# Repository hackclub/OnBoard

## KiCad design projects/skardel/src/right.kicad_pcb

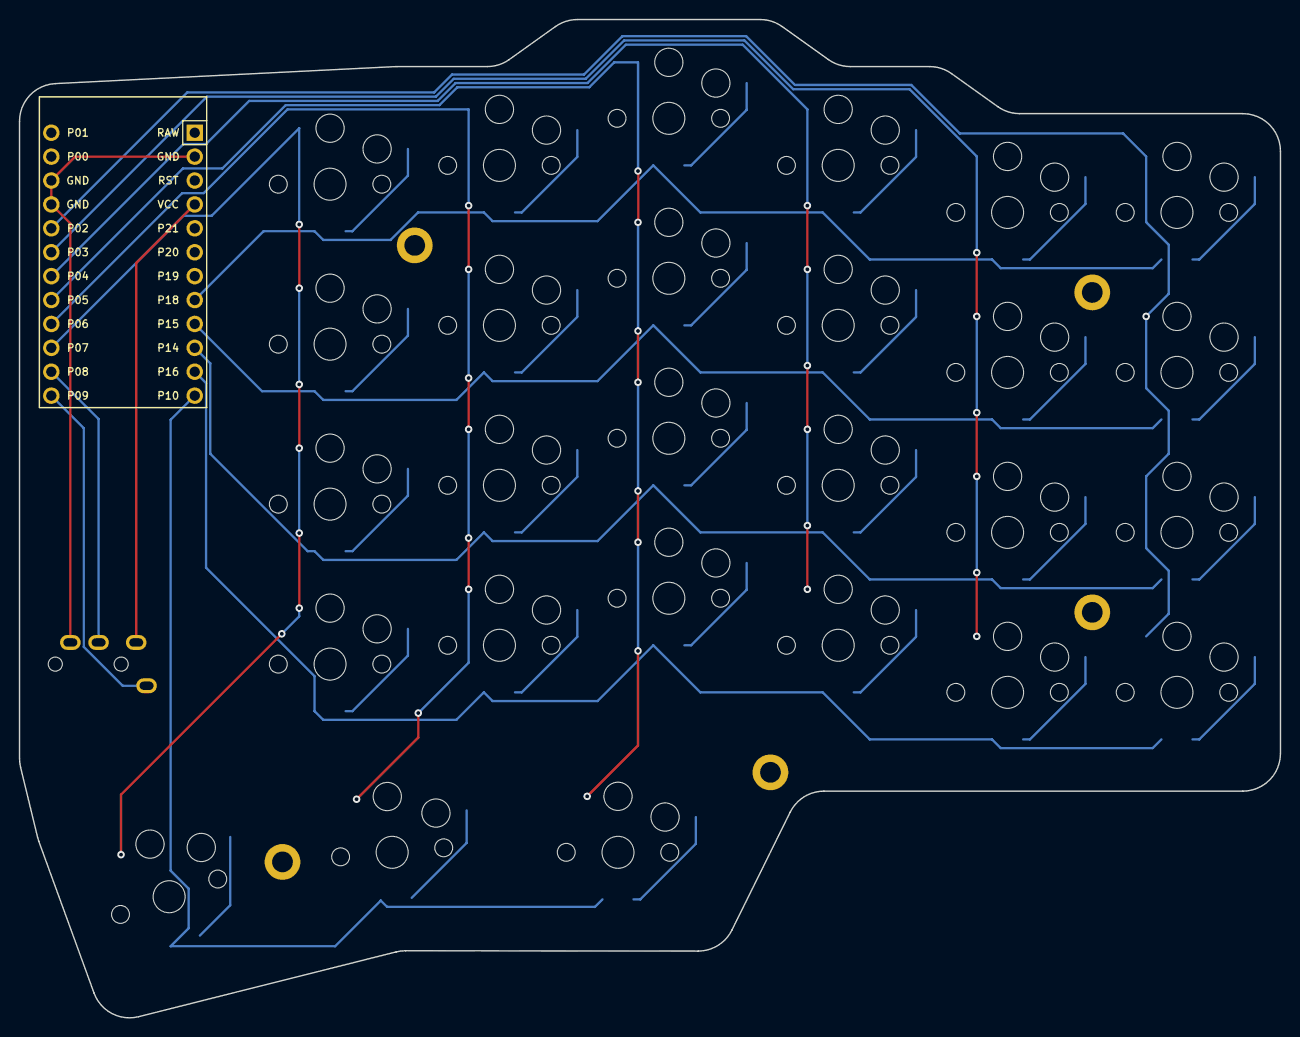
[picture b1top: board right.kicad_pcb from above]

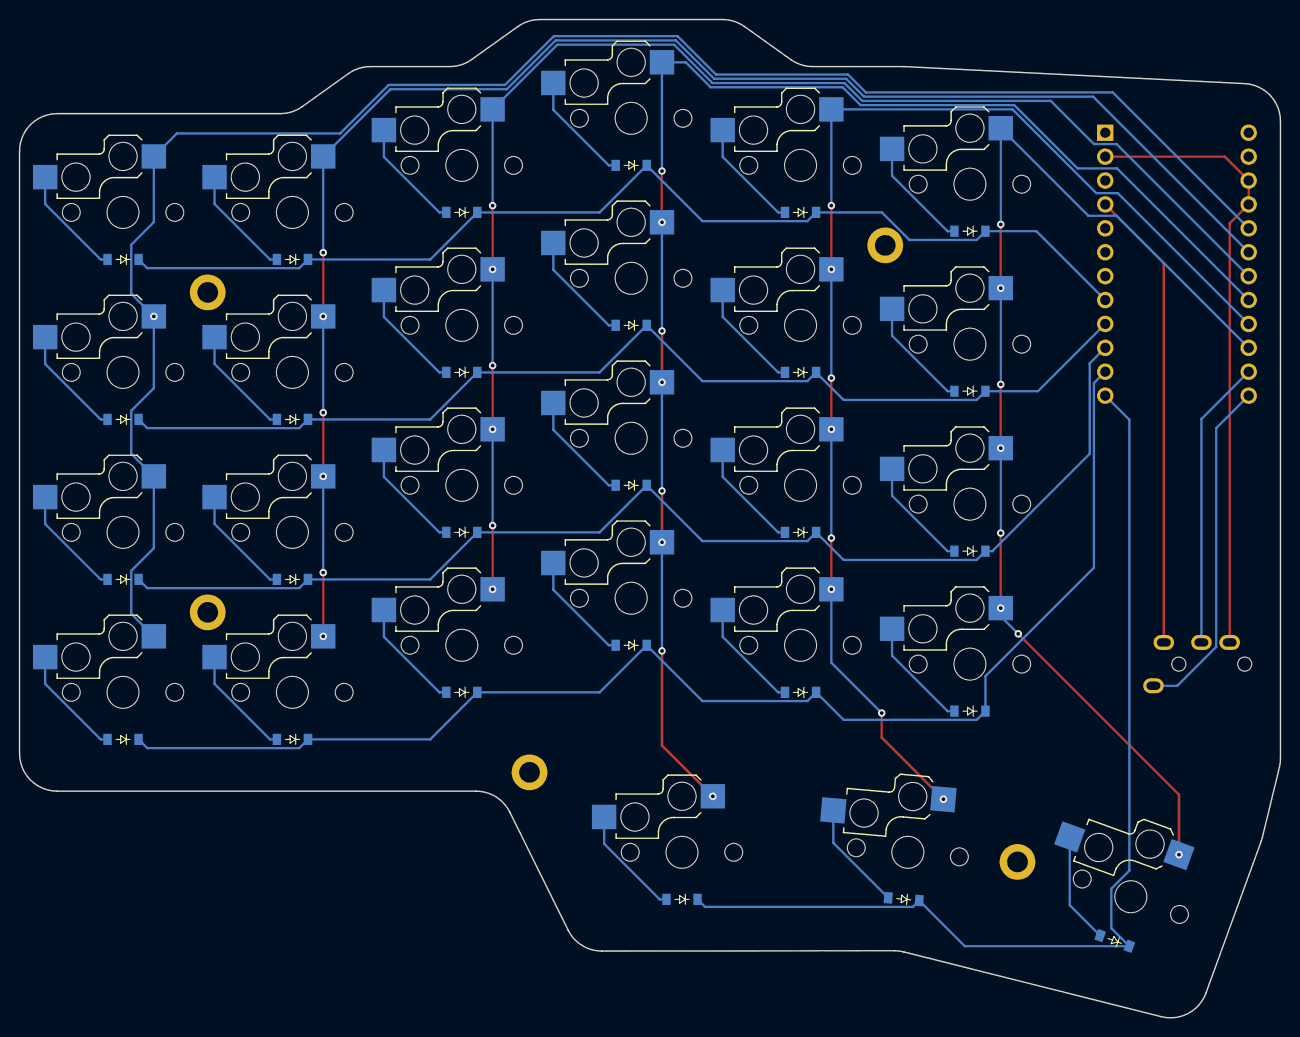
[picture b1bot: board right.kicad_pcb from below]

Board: 2 copper layers, 134.0 x 106.1 mm, 61 parts (54 on the bottom side), 42 nets.

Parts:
D1, D2, D3, D4, D5, D6, D7, D8, D9, D10, D11, D12, D13, D14, D15, D16, D17, D18, D19, D20, D21, D22, D23, D24, D25, D26, D27: diode_tht_sod123
H1, H2, H3, H4, H5: mounting_hole_plated
MCU1: ProMicro
S1, S2, S3, S4, S5, S6, S7, S8, S9, S10, S11, S12, S13, S14, S15, S16, S17, S18, S19, S20, S21, S22, S23, S24, S25, S26, S27: switch_choc_v1_v2
TRRS1: trrs_pj320a

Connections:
GND: MCU1.2, MCU1.15, MCU1.16, TRRS1.2
P2: MCU1.17, S1.1, S2.1, S3.1, S4.1
P3: MCU1.18, S5.1, S6.1, S7.1, S8.1
P4: MCU1.19, S9.1, S10.1, S11.1, S12.1
P5: MCU1.20, S13.1, S14.1, S15.1, S16.1, S25.1
P6: MCU1.21, S17.1, S18.1, S19.1, S20.1, S26.1
P7: MCU1.22, S21.1, S22.1, S23.1, S24.1, S27.1
P8: MCU1.23, TRRS1.3
P9: MCU1.24, TRRS1.5
P10: D25.1, D26.1, D27.1, MCU1.12
P14: D2.1, D6.1, D10.1, D14.1, D18.1, D22.1, MCU1.10
P15: D3.1, D7.1, D11.1, D15.1, D19.1, D23.1, MCU1.9
P16: D1.1, D5.1, D9.1, D13.1, D17.1, D21.1, MCU1.11
P18: D4.1, D8.1, D12.1, D16.1, D20.1, D24.1, MCU1.8
VCC: MCU1.4, TRRS1.4
mirror_home_home: D26.2, S26.2
mirror_in_home: D27.2, S27.2
mirror_index_bottom: D17.2, S17.2
mirror_index_home: D18.2, S18.2
mirror_index_num: D20.2, S20.2
mirror_index_top: D19.2, S19.2
mirror_inner_bottom: D21.2, S21.2
mirror_inner_home: D22.2, S22.2
mirror_inner_num: D24.2, S24.2
mirror_inner_top: D23.2, S23.2
mirror_middle_bottom: D13.2, S13.2
mirror_middle_home: D14.2, S14.2
mirror_middle_num: D16.2, S16.2
mirror_middle_top: D15.2, S15.2
mirror_out_home: D25.2, S25.2
mirror_outer_bottom: D1.2, S1.2
mirror_outer_home: D2.2, S2.2
mirror_outer_num: D4.2, S4.2
mirror_outer_top: D3.2, S3.2
mirror_pinky_bottom: D5.2, S5.2
mirror_pinky_home: D6.2, S6.2
mirror_pinky_num: D8.2, S8.2
mirror_pinky_top: D7.2, S7.2
mirror_ring_bottom: D9.2, S9.2
mirror_ring_home: D10.2, S10.2
mirror_ring_num: D12.2, S12.2
mirror_ring_top: D11.2, S11.2

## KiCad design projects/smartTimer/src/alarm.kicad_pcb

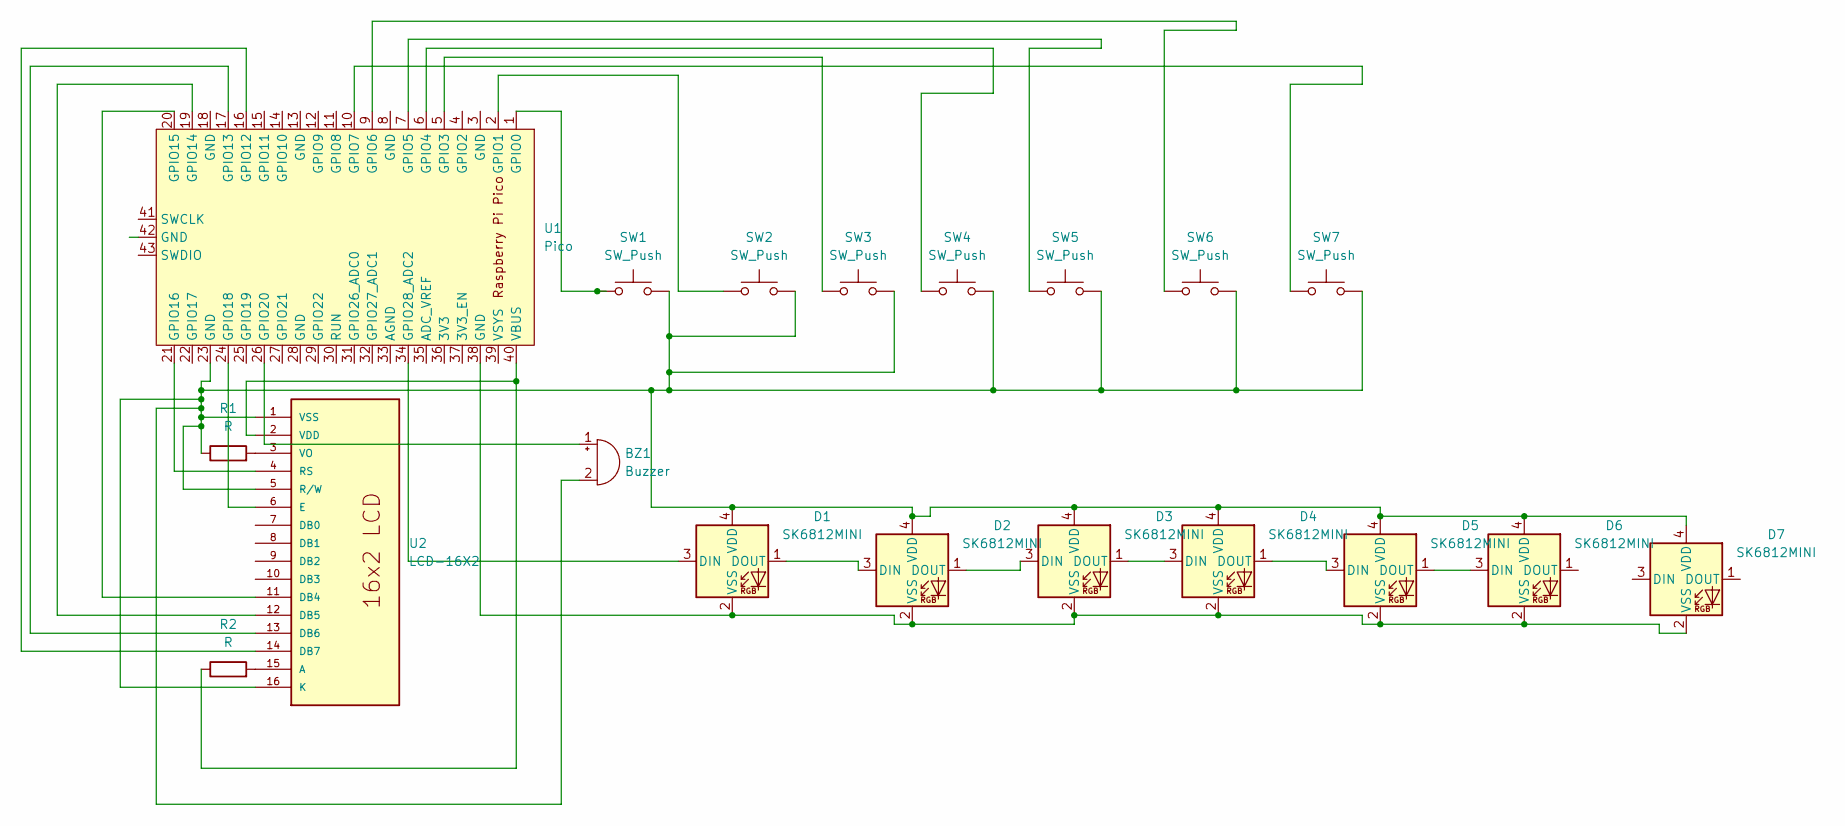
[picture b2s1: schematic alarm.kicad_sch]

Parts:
BZ1: Buzzer; Buzzer_12x9.5RM7.6
D1, D2, D3, D4, D5, D6, D7: SK6812MINI; LED_SK6812MINI_PLCC4_3.5x3.5mm_P1.75mm
R1, R2: R; R_Axial_DIN0204_L3.6mm_D1.6mm_P5.08mm_Horizontal
SW1, SW2, SW3, SW4, SW5, SW6, SW7: SW_Push; SW_PUSH_6mm
U1: Pico; RaspberryPi_Pico_W_SMD
U2: LCD-16X2; MODULE_LCD-16X2; PARTREV N/A

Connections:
unnamed: BZ1.1 (+), U1.26 (GPIO20)
unnamed: BZ1.2 (-), D1.4 (VDD), D2.4 (VDD), D3.4 (VDD), D4.4 (VDD), D5.4 (VDD), D6.4 (VDD), D7.4 (VDD), R1.1, SW1.2, SW2.2, SW3.2, SW4.2, SW5.2, SW6.2, SW7.2, U1.23 (GND), U2.1 (VSS), U2.5 (R/W), U2.16 (K)
unnamed: D1.3 (DIN), U1.34 (GPIO28_ADC2)
unnamed: D1.1 (DOUT), D2.3 (DIN)
unnamed: D1.2 (VSS), D2.2 (VSS), D3.2 (VSS), D4.2 (VSS), D5.2 (VSS), D6.2 (VSS), D7.2 (VSS), U1.38 (GND)
unnamed: D2.1 (DOUT), D3.3 (DIN)
unnamed: D3.1 (DOUT), D4.3 (DIN)
unnamed: D4.1 (DOUT), D5.3 (DIN)
unnamed: D5.1 (DOUT), D6.3 (DIN)
unnamed: SW1.1, U1.1 (GPIO0)
unnamed: SW2.1, U1.2 (GPIO1)
unnamed: SW3.1, U1.5 (GPIO3)
unnamed: SW4.1, U1.6 (GPIO4)
unnamed: SW5.1, U1.7 (GPIO5)
unnamed: SW6.1, U1.9 (GPIO6)
unnamed: SW7.1, U1.10 (GPIO7)
unnamed: U1.16 (GPIO12), U2.14 (DB7)
unnamed: U1.17 (GPIO13), U2.13 (DB6)
unnamed: U1.19 (GPIO14), U2.12 (DB5)
unnamed: U1.20 (GPIO15), U2.11 (DB4)
unnamed: U1.21 (GPIO16), U2.4 (RS)
unnamed: U1.24 (GPIO18), U2.6 (E)
unnamed: R2.1, U1.40 (VBUS), U2.2 (VDD)
unnamed: R2.2, U2.15 (A)
unnamed: R1.2, U2.3 (VO)

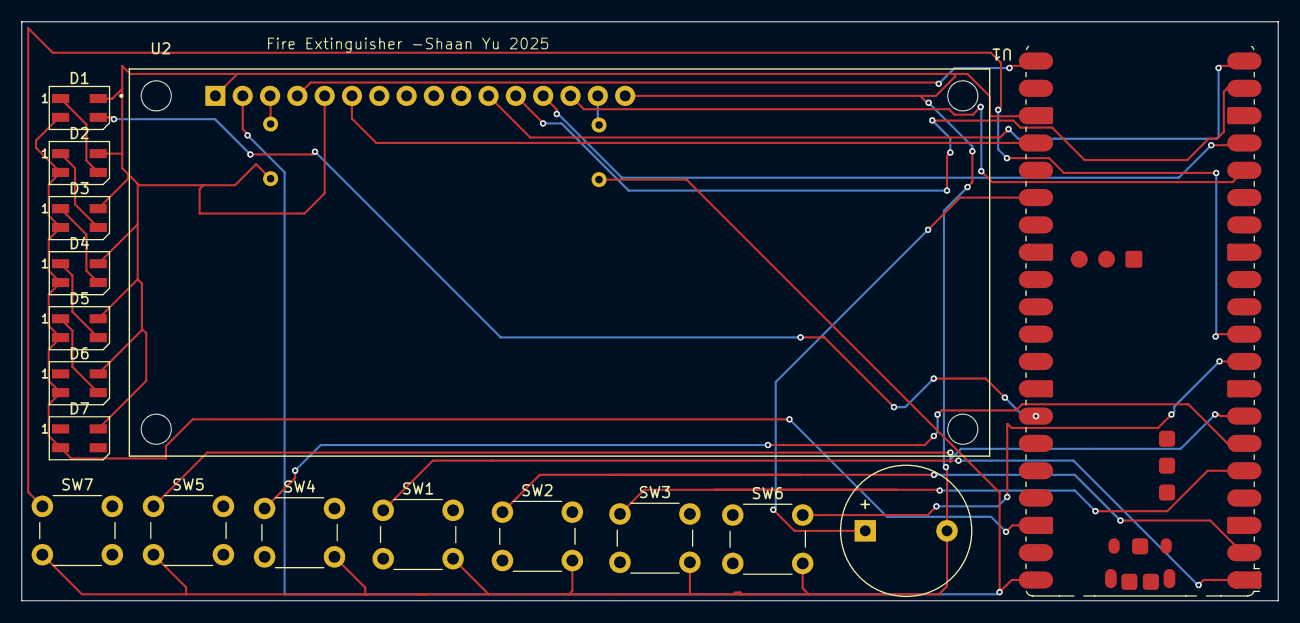
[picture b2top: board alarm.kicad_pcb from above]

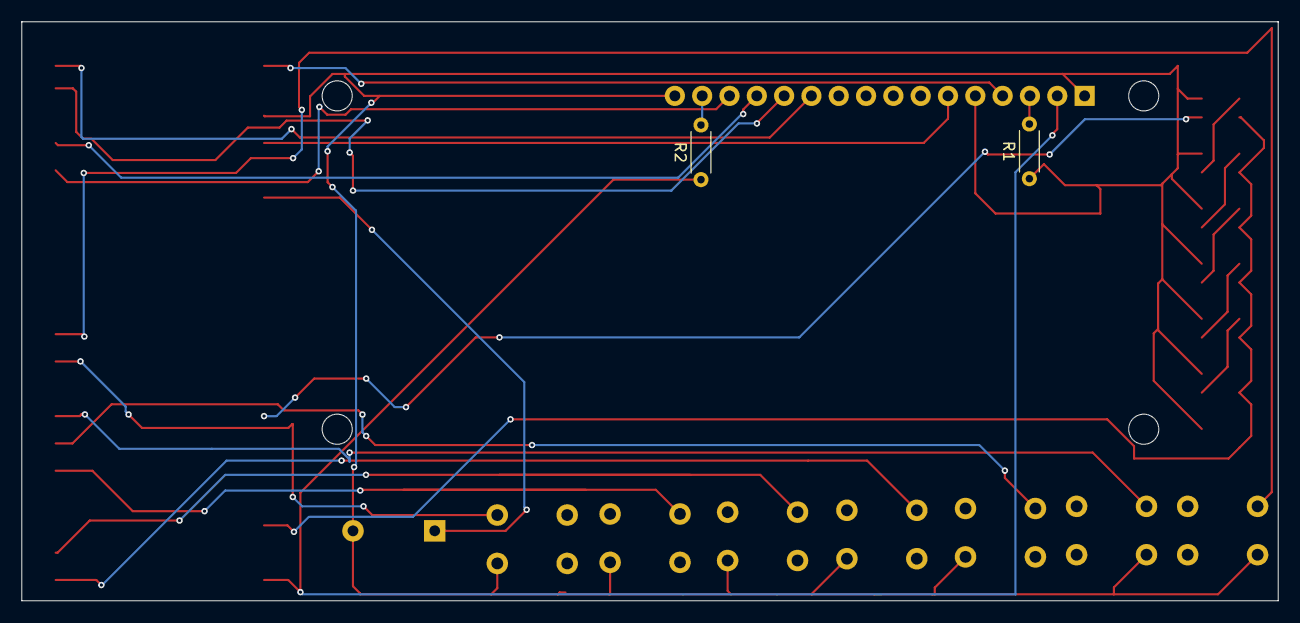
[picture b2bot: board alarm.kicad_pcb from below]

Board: 2 copper layers, 116.8 x 53.8 mm, 19 parts (2 on the bottom side), 25 nets.

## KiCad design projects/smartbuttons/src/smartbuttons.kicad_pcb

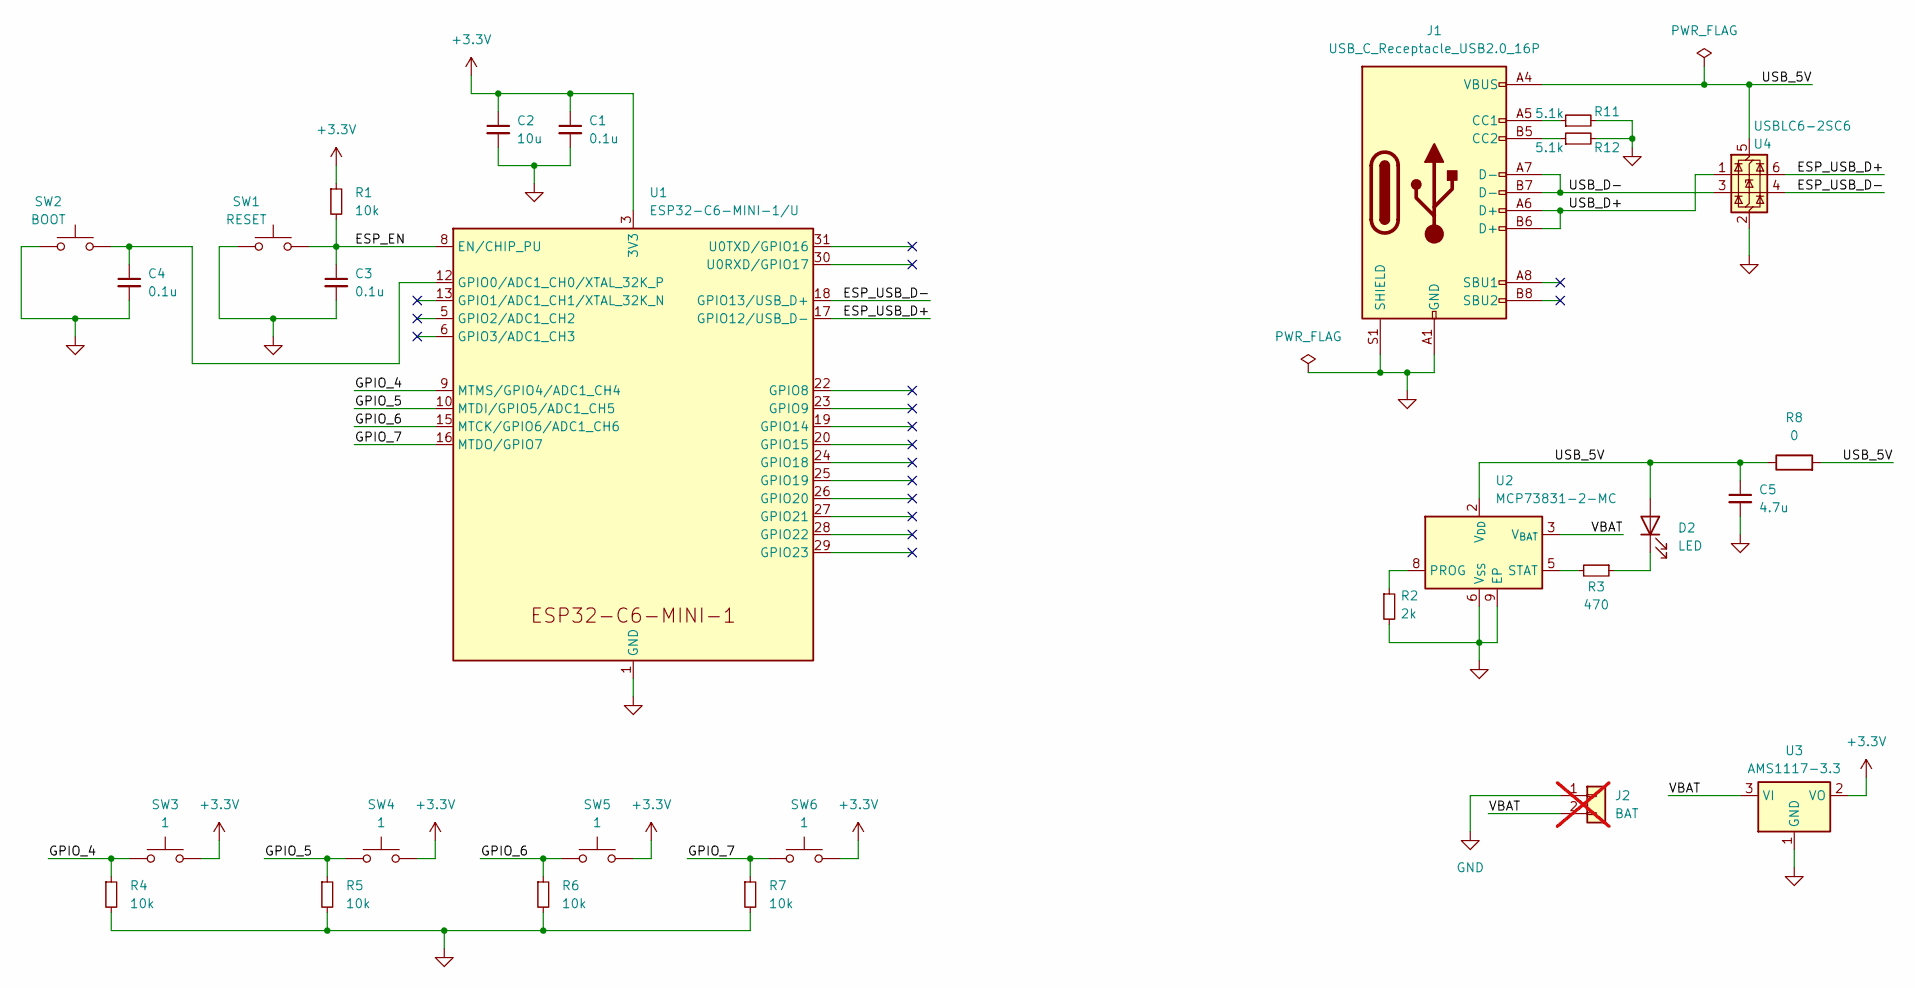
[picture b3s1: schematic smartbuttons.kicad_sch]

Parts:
C1, C3, C4: 0.1u; C_0402_1005Metric; LCSC C1525
C2: 10u; C_0805_2012Metric; LCSC C440198
C5: 4.7u; C_0805_2012Metric; LCSC C1779
D2: LED; LED_0805_2012Metric; LCSC C2296
J1: USB_C_Receptacle_USB2.0_16P; USB_C_Receptacle_HCTL_HC-TYPE-C-16P-01A; LCSC C2894897
J2: BAT; SolderWirePad_3; not fitted
R1, R4, R5, R6, R7: 10k; R_0402_1005Metric; LCSC C25744
R2: 2k; R_0402_1005Metric; LCSC C4109
R3: 470; R_0402_1005Metric; LCSC C25117
R8: 0; R_0805_2012Metric; LCSC C431818
R11, R12: 5.1k; R_0402_1005Metric; LCSC C25905
SW1: RESET; SW-SMD_L3.9-W3.0-P4.45; LCSC C115357
SW2: BOOT; SW-SMD_L3.9-W3.0-P4.45; LCSC C115357
SW3, SW4, SW5, SW6: 1; SW_Kailh_Choc_V1_THT; LCSC C400229
U1: ESP32-C6-MINI-1/U; ESP32-C6-MINI-1; LCSC C5736265
U2: MCP73831-2-MC; DFN-8-1EP_3x2mm_P0.5mm_EP1.7x1.4mm; LCSC C635037
U3: AMS1117-3.3; SOT-223-3_TabPin2; LCSC C6186
U4: USBLC6-2SC6; SOT-23-6; LCSC C7519

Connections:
+3.3V: C1.1, C2.1, R1.1, SW3.2, SW4.2, SW5.2, SW6.2, U1.3 (3V3), U3.2 (VO)
/ESP_EN: C3.1, R1.2, SW1.2, U1.8 (EN/CHIP_PU)
/ESP_USB_D+: U1.17 (GPIO12/USB_D-), U4.6 (I/O1)
/ESP_USB_D-: U1.18 (GPIO13/USB_D+), U4.4 (I/O2)
/GPIO_4: R4.1, SW3.1, U1.9 (MTMS/GPIO4/ADC1_CH4)
/GPIO_5: R5.1, SW4.1, U1.10 (MTDI/GPIO5/ADC1_CH5)
/GPIO_6: R6.1, SW5.1, U1.15 (MTCK/GPIO6/ADC1_CH6)
/GPIO_7: R7.1, SW6.1, U1.16 (MTDO/GPIO7)
/USB_5V: C5.1, D2.2 (A), J1.A4 (VBUS), J1.A9 (VBUS), J1.B4 (VBUS), J1.B9 (VBUS), R8.1, R8.2, U2.1 (V_{DD}), U2.2 (V_{DD}), U4.5 (VBUS)
/USB_D+: J1.A6 (D+), J1.B6 (D+), U4.1 (I/O1)
/USB_D-: J1.A7 (D-), J1.B7 (D-), U4.3 (I/O2)
/VBAT: J2.2, U2.3 (V_{BAT}), U2.4 (V_{BAT}), U3.3 (VI)
GND: C1.2, C2.2, C3.2, C4.2, C5.2, J1.A1 (GND), J1.A12 (GND), J1.B1 (GND), J1.B12 (GND), J1.S1 (SHIELD), J2.1, R2.2, R4.2, R5.2, R6.2, R7.2, R11.2, R12.2, SW1.1, SW2.1, U1.1 (GND), U1.2 (GND), U1.11 (GND), U1.14 (GND), U1.36 (GND), U1.37 (GND), U1.38 (GND), U1.39 (GND), U1.40 (GND), U1.41 (GND), U1.42 (GND), U1.43 (GND), U1.44 (GND), U1.45 (GND), U1.46 (GND), U1.47 (GND), U1.48 (GND), U1.49 (GND), U1.50 (GND), U1.51 (GND), U1.52 (GND), U1.53 (GND), U2.6 (V_{SS}), U2.9 (EP), U3.1 (GND), U4.2 (GND)
unnamed: D2.1 (K), R3.1
unnamed: J1.A5 (CC1), R11.1
unnamed: J1.B5 (CC2), R12.1
unnamed: C4.1, SW2.2, U1.12 (GPIO0/ADC1_CH0/XTAL_32K_P)
unnamed: R2.1, U2.8 (PROG)
unnamed: R3.2, U2.5 (STAT)

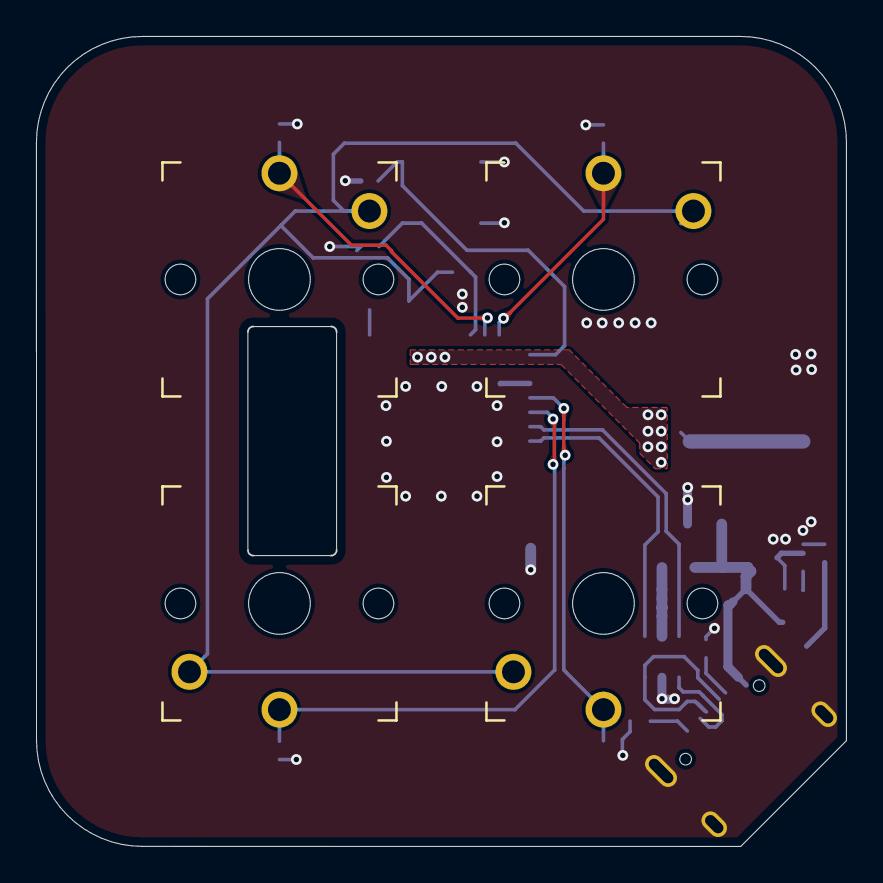
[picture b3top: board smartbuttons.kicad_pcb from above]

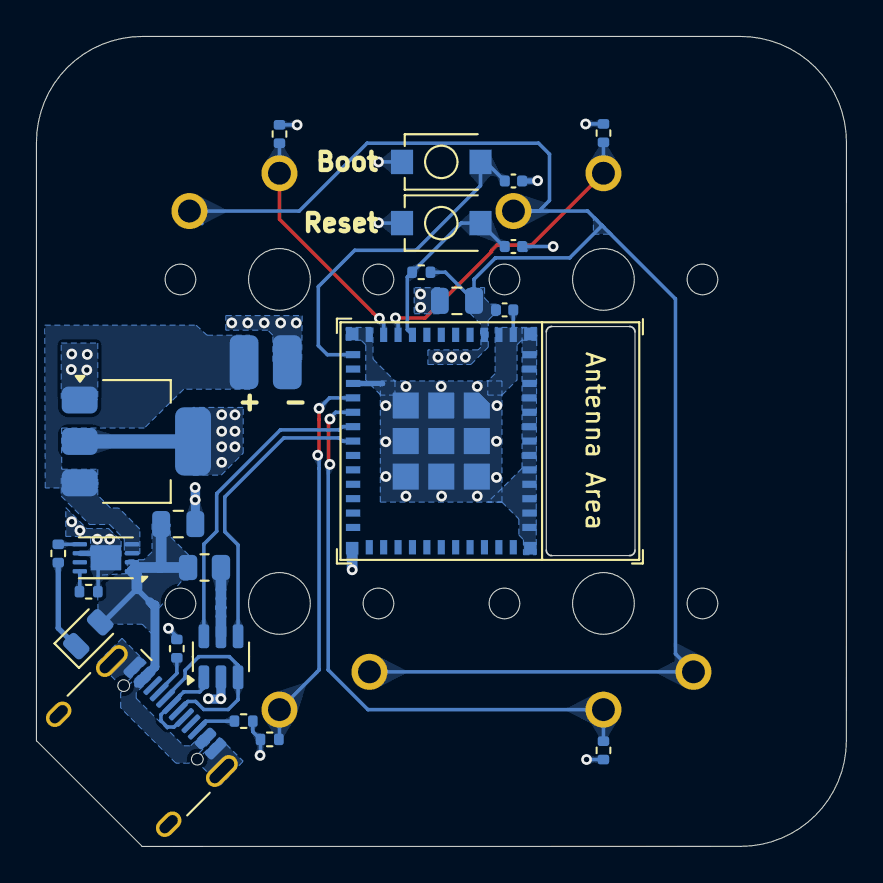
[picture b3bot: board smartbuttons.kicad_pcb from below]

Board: 2 copper layers, 45.0 x 45.0 mm, 28 parts (24 on the bottom side), 19 nets.

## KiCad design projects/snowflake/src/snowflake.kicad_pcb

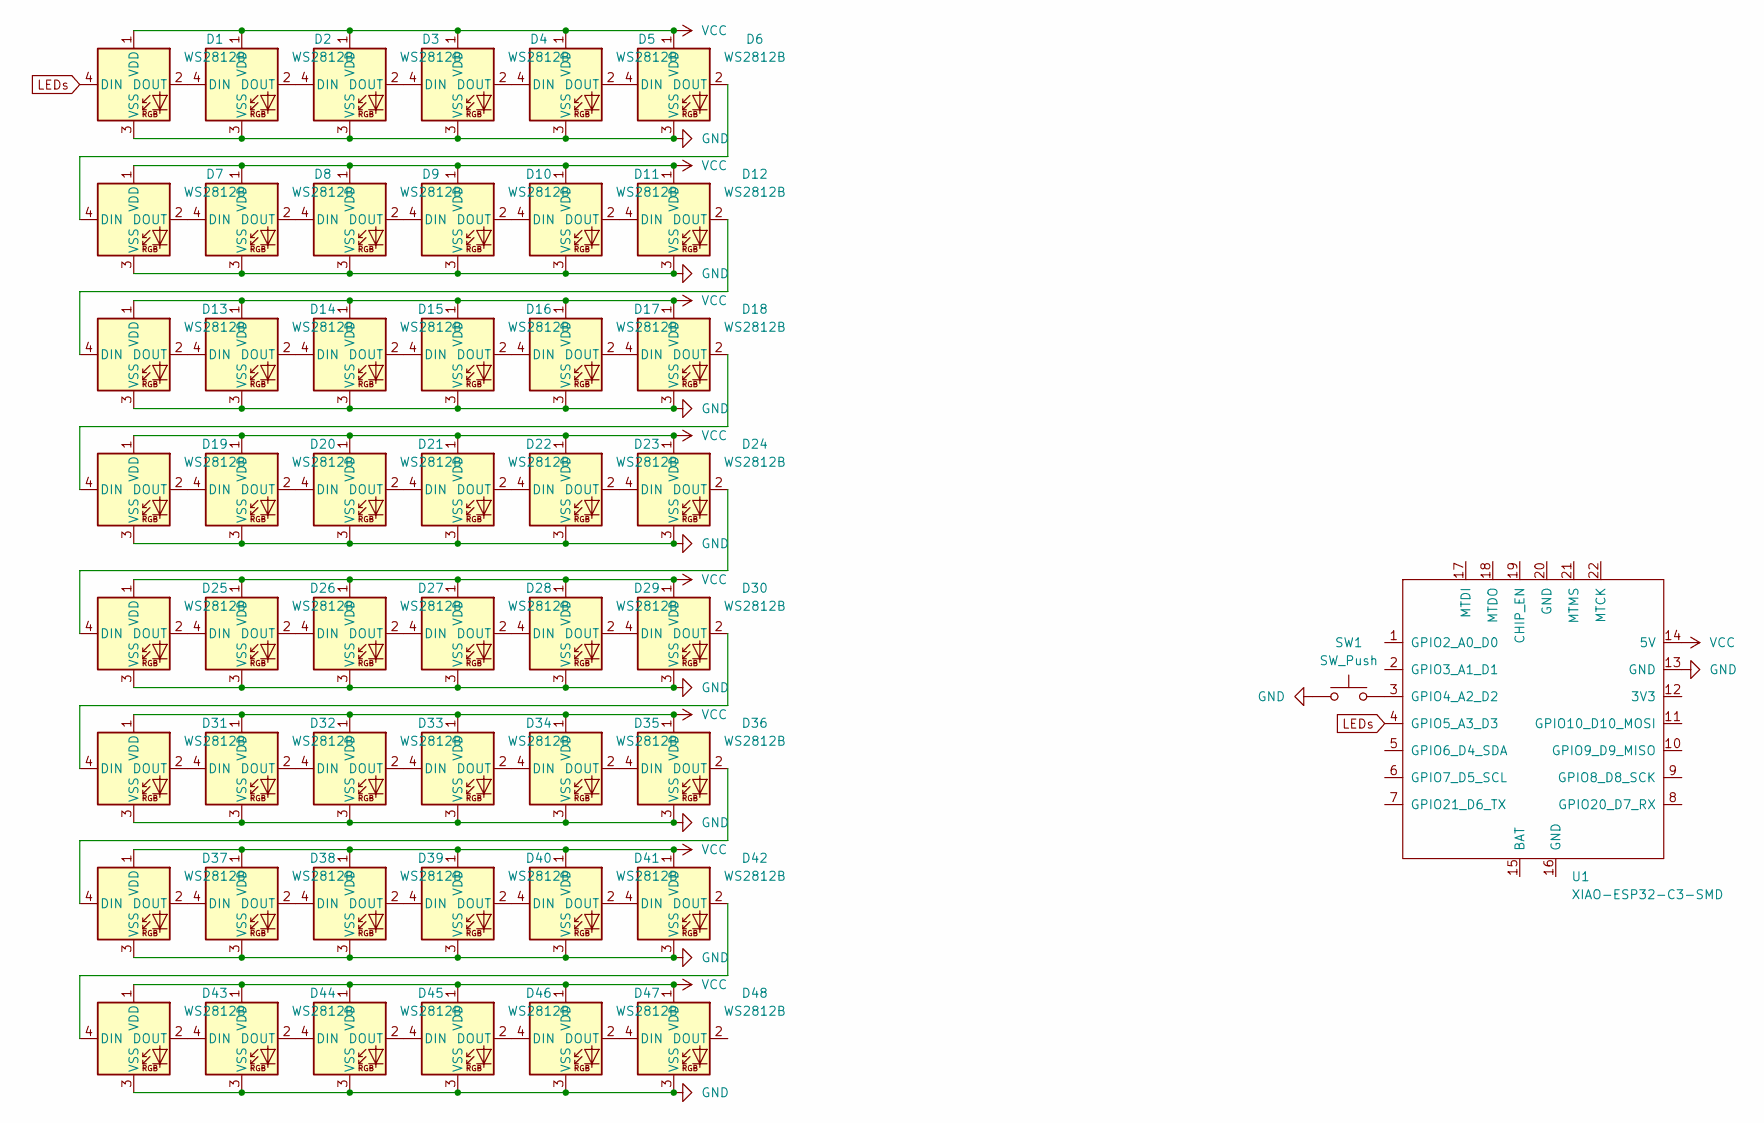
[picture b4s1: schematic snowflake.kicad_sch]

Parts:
D1, D2, D3, D4, D5, D6, D7, D8, D9, D10, D11, D12, D13, D14, D15, D16, D17, D18, D19, D20, D21, D22, D23, D24, D25, D26, D27, D28, D29, D30, D31, D32, D33, D34, D35, D36, D37, D38, D39, D40, D41, D42, D43, D44, D45, D46, D47, D48: WS2812B; LED_WS2812B_PLCC4_5.0x5.0mm_P3.2mm
SW1: SW_Push; SW-SMD_4P-L5.1-W5.1-P3.70-LS6.5-TL_H1.5
U1: XIAO-ESP32-C3-SMD; XIAO-ESP32S3-SMD

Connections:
GND: D1.3 (VSS), D2.3 (VSS), D3.3 (VSS), D4.3 (VSS), D5.3 (VSS), D6.3 (VSS), D7.3 (VSS), D8.3 (VSS), D9.3 (VSS), D10.3 (VSS), D11.3 (VSS), D12.3 (VSS), D13.3 (VSS), D14.3 (VSS), D15.3 (VSS), D16.3 (VSS), D17.3 (VSS), D18.3 (VSS), D19.3 (VSS), D20.3 (VSS), D21.3 (VSS), D22.3 (VSS), D23.3 (VSS), D24.3 (VSS), D25.3 (VSS), D26.3 (VSS), D27.3 (VSS), D28.3 (VSS), D29.3 (VSS), D30.3 (VSS), D31.3 (VSS), D32.3 (VSS), D33.3 (VSS), D34.3 (VSS), D35.3 (VSS), D36.3 (VSS), D37.3 (VSS), D38.3 (VSS), D39.3 (VSS), D40.3 (VSS), D41.3 (VSS), D42.3 (VSS), D43.3 (VSS), D44.3 (VSS), D45.3 (VSS), D46.3 (VSS), D47.3 (VSS), D48.3 (VSS), SW1.1, U1.13 (GND)
LEDs: D1.4 (DIN), U1.4 (GPIO5_A3_D3)
unnamed: D1.2 (DOUT), D2.4 (DIN)
unnamed: D2.2 (DOUT), D3.4 (DIN)
unnamed: D3.2 (DOUT), D4.4 (DIN)
unnamed: D4.2 (DOUT), D5.4 (DIN)
unnamed: D5.2 (DOUT), D6.4 (DIN)
unnamed: D6.2 (DOUT), D7.4 (DIN)
unnamed: D7.2 (DOUT), D8.4 (DIN)
unnamed: D8.2 (DOUT), D9.4 (DIN)
unnamed: D9.2 (DOUT), D10.4 (DIN)
unnamed: D10.2 (DOUT), D11.4 (DIN)
unnamed: D11.2 (DOUT), D12.4 (DIN)
unnamed: D12.2 (DOUT), D13.4 (DIN)
unnamed: D13.2 (DOUT), D14.4 (DIN)
unnamed: D14.2 (DOUT), D15.4 (DIN)
unnamed: D15.2 (DOUT), D16.4 (DIN)
unnamed: D16.2 (DOUT), D17.4 (DIN)
unnamed: D17.2 (DOUT), D18.4 (DIN)
unnamed: D18.2 (DOUT), D19.4 (DIN)
unnamed: D19.2 (DOUT), D20.4 (DIN)
unnamed: D20.2 (DOUT), D21.4 (DIN)
unnamed: D21.2 (DOUT), D22.4 (DIN)
unnamed: D22.2 (DOUT), D23.4 (DIN)
unnamed: D23.2 (DOUT), D24.4 (DIN)
unnamed: D24.2 (DOUT), D25.4 (DIN)
unnamed: D25.2 (DOUT), D26.4 (DIN)
unnamed: D26.2 (DOUT), D27.4 (DIN)
unnamed: D27.2 (DOUT), D28.4 (DIN)
unnamed: D28.2 (DOUT), D29.4 (DIN)
unnamed: D29.2 (DOUT), D30.4 (DIN)
unnamed: D30.2 (DOUT), D31.4 (DIN)
unnamed: D31.2 (DOUT), D32.4 (DIN)
unnamed: D32.2 (DOUT), D33.4 (DIN)
unnamed: D33.2 (DOUT), D34.4 (DIN)
unnamed: D34.2 (DOUT), D35.4 (DIN)
unnamed: D35.2 (DOUT), D36.4 (DIN)
unnamed: D36.2 (DOUT), D37.4 (DIN)
unnamed: D37.2 (DOUT), D38.4 (DIN)
unnamed: D38.2 (DOUT), D39.4 (DIN)
unnamed: D39.2 (DOUT), D40.4 (DIN)
unnamed: D40.2 (DOUT), D41.4 (DIN)
unnamed: D41.2 (DOUT), D42.4 (DIN)
unnamed: D42.2 (DOUT), D43.4 (DIN)
unnamed: D43.2 (DOUT), D44.4 (DIN)
unnamed: D44.2 (DOUT), D45.4 (DIN)
unnamed: D45.2 (DOUT), D46.4 (DIN)
unnamed: D46.2 (DOUT), D47.4 (DIN)
unnamed: D47.2 (DOUT), D48.4 (DIN)
unnamed: SW1.2, U1.3 (GPIO4_A2_D2)
VCC: D1.1 (VDD), D2.1 (VDD), D3.1 (VDD), D4.1 (VDD), D5.1 (VDD), D6.1 (VDD), D7.1 (VDD), D8.1 (VDD), D9.1 (VDD), D10.1 (VDD), D11.1 (VDD), D12.1 (VDD), D13.1 (VDD), D14.1 (VDD), D15.1 (VDD), D16.1 (VDD), D17.1 (VDD), D18.1 (VDD), D19.1 (VDD), D20.1 (VDD), D21.1 (VDD), D22.1 (VDD), D23.1 (VDD), D24.1 (VDD), D25.1 (VDD), D26.1 (VDD), D27.1 (VDD), D28.1 (VDD), D29.1 (VDD), D30.1 (VDD), D31.1 (VDD), D32.1 (VDD), D33.1 (VDD), D34.1 (VDD), D35.1 (VDD), D36.1 (VDD), D37.1 (VDD), D38.1 (VDD), D39.1 (VDD), D40.1 (VDD), D41.1 (VDD), D42.1 (VDD), D43.1 (VDD), D44.1 (VDD), D45.1 (VDD), D46.1 (VDD), D47.1 (VDD), D48.1 (VDD), U1.14 (5V)

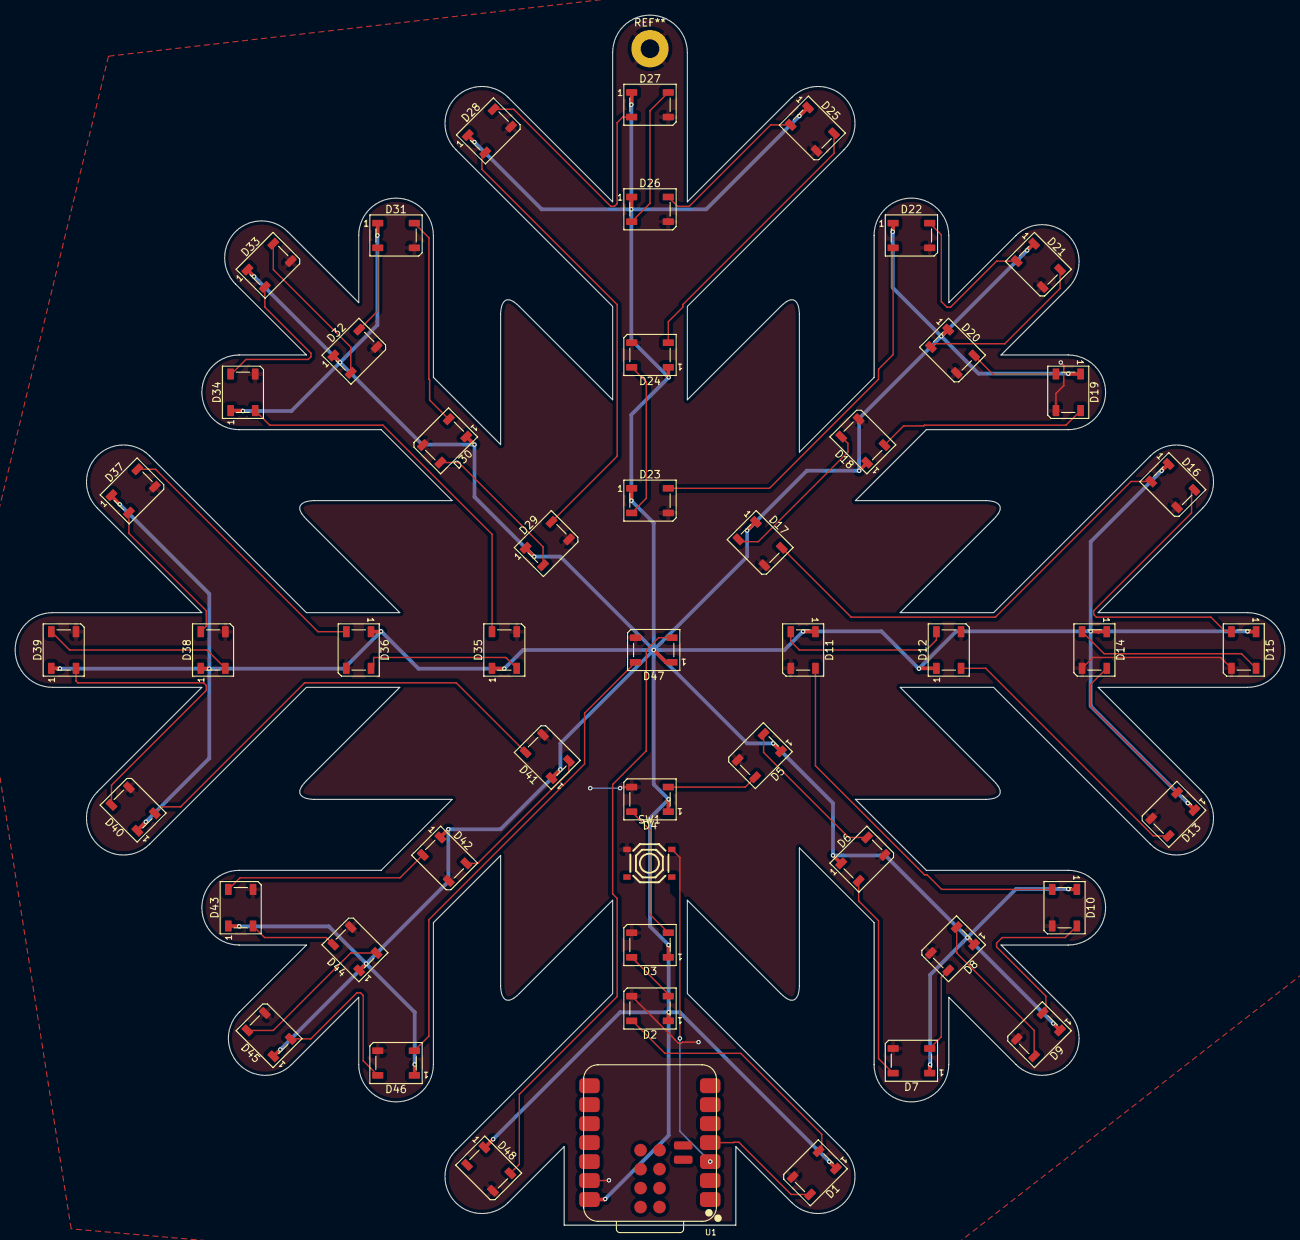
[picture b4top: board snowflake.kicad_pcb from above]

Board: 2 copper layers, 170.0 x 162.0 mm, 50 parts (0 on the bottom side), 51 nets.

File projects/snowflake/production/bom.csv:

Designator,Footprint,Quantity,Value,LCSC Part #
"D1, D10, D11, D12, D13, D14, D15, D16, D17, D18, D19, D2, D20, D21, D22, D23, D24, D25, D26, D27, D28, D29, D3, D30, D31, D32, D33, D34, D35, D36, D37, D38, D39, D4, D40, D41, D42, D43, D44, D45, D46, D47, D48, D5, D6, D7, D8, D9",LED_WS2812B_PLCC4_5.0x5.0mm_P3.2mm,48,WS2812B,C22461793
SW1,SW-SMD_4P-L5.1-W5.1-P3.70-LS6.5-TL_H1.5,1,SW_Push,C318884
U1,XIAO-ESP32S3-SMD,1,XIAO-ESP32-C3-SMD,

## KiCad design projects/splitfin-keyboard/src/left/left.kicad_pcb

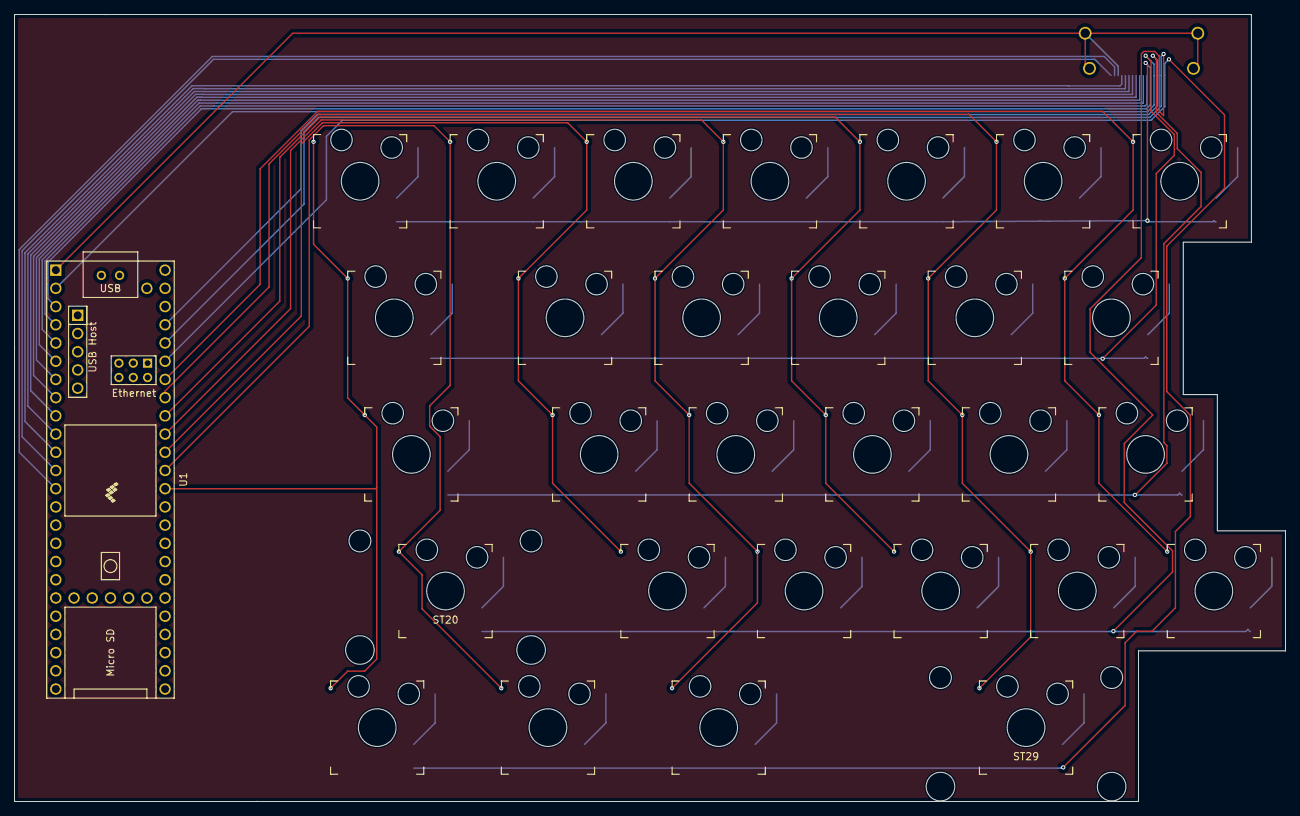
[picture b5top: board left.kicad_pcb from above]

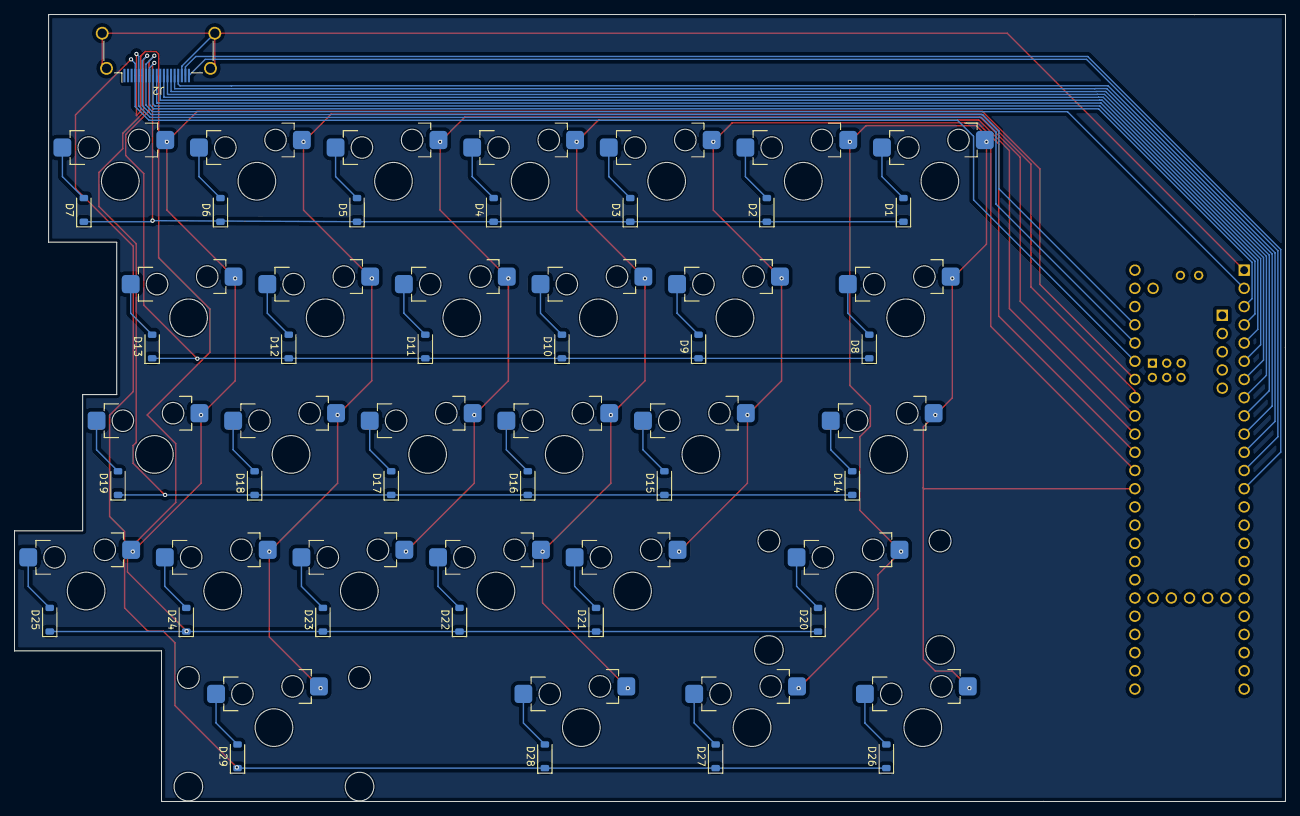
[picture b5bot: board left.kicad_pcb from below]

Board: 2 copper layers, 177.2 x 109.8 mm, 62 parts (30 on the bottom side), 52 nets.

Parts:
D1, D2, D3, D4, D5, D6, D7, D8, D9, D10, D11, D12, D13, D14, D15, D16, D17, D18, D19, D20, D21, D22, D23, D24, D25, D26, D27, D28, D29: D; D_SOD-123
J2: HDMI_A; HDMI_A_Amphenol_10029449-x01xLF_Horizontal
ST20, ST29: MountingHole; Stabilizer_Cherry_MX_2.00u
SW1, SW2, SW3, SW4, SW5, SW6, SW7, SW8, SW9, SW10, SW11, SW12, SW13, SW14, SW15, SW16, SW17, SW18, SW19, SW20, SW21, SW22, SW23, SW24, SW25, SW26, SW27, SW28, SW29: SW_Push; SW_Gateron_LowProfile_HotSwap_Good
U1: Teensy4.1; Teensy41

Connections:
COL0: SW1.1, SW8.1, SW14.1, SW26.1, U1.36 (14_A0_TX3_SPDIF_OUT)
COL1: SW2.1, SW20.1, SW27.1, U1.37 (15_A1_RX3_SPDIF_IN)
COL2: SW3.1, SW9.1, SW15.1, SW21.1, U1.38 (16_A2_RX4_SCL1)
COL3: SW4.1, SW10.1, SW16.1, SW22.1, SW28.1, U1.39 (17_A3_TX4_SDA1)
COL4: SW5.1, SW11.1, SW17.1, SW23.1, U1.40 (18_A4_SDA)
COL5: SW6.1, SW12.1, SW18.1, SW24.1, SW29.1, U1.41 (19_A5_SCL)
COL6: SW7.1, SW13.1, SW19.1, SW25.1, U1.42 (20_A6_TX5_LRCLK1)
GND: J2.17 (GND), J2.SH, U1.1 (GND)
unnamed: D1.2, SW1.2
unnamed: D2.2, SW2.2
unnamed: D3.2, SW3.2
unnamed: D4.2, SW4.2
unnamed: D5.2, SW5.2
unnamed: D6.2, SW6.2
unnamed: D7.2, SW7.2
unnamed: D8.2, SW8.2
unnamed: D9.2, SW9.2
unnamed: D10.2, SW10.2
unnamed: D11.2, SW11.2
unnamed: D12.2, SW12.2
unnamed: D13.2, SW13.2
unnamed: D14.2, SW14.2
unnamed: D15.2, SW15.2
unnamed: D16.2, SW16.2
unnamed: D17.2, SW17.2
unnamed: D18.2, SW18.2
unnamed: D19.2, SW19.2
unnamed: D20.2, SW20.2
unnamed: D21.2, SW21.2
unnamed: D22.2, SW22.2
unnamed: D23.2, SW23.2
unnamed: D24.2, SW24.2
unnamed: D25.2, SW25.2
unnamed: D26.2, SW26.2
unnamed: D27.2, SW27.2
unnamed: D28.2, SW28.2
unnamed: D29.2, SW29.2
RCOL0: J2.18 (+5V), U1.13 (11_MOSI_CTX1)
RCOL1: J2.19 (HPD), U1.12 (10_CS_MQSR)
RCOL2: J2.16 (SDA), U1.11 (9_OUT1C)
RCOL3: J2.15 (SCL), U1.10 (8_TX2_IN1)
RCOL4: J2.14 (UTILITY), U1.9 (7_RX2_OUT1A)
RCOL5: J2.13 (CEC), U1.8 (6_OUT1D)
RCOL6: J2.12 (CK-), U1.7 (5_IN2)
RCOL7: J2.11 (CKS), U1.6 (4_BCLK2)
RCOL8: J2.10 (CK+), U1.5 (3_LRCLK2)
RCOL9: J2.9 (D0-), U1.4 (2_OUT2)
ROW0: D1.1, D2.1, D3.1, D4.1, D5.1, D6.1, D7.1, J2.8 (D0S), U1.3 (1_TX1_CTX2_MISO1)
ROW1: D8.1, D9.1, D10.1, D11.1, D12.1, D13.1, J2.7 (D0+), U1.2 (0_RX1_CRX2_CS1)
ROW2: D14.1, D15.1, D16.1, D17.1, D18.1, D19.1, J2.6 (D1-), U1.45 (23_A9_CRX1_MCLK1)
ROW3: D20.1, D21.1, D22.1, D23.1, D24.1, D25.1, J2.5 (D1S), U1.44 (22_A8_CTX1)
ROW4: D26.1, D27.1, D28.1, D29.1, J2.4 (D1+), U1.43 (21_A7_RX5_BCLK1)
